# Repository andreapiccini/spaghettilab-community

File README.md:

<p align="center">
  <a href="https://spaghetti-lab.my.canva.site/">Website</a> •
  <a href="https://spaghetti-lab.my.canva.site/join-newsletter">Newsletter</a>
</p>

# SpaghettiLAB Community

From prototype to product.

SpaghettiLAB Community is the open development platform for learning,
experimenting, and building modular embedded and IoT prototypes. It includes
reference hardware, firmware, local software, protocols, integrations, tests,
and examples without artificial feature restrictions.

A prototype is not automatically suitable for production. Professional
deployments also require qualified hardware, secure provisioning, verified
updates, release traceability, lifecycle maintenance, and accountable support.
Those production capabilities are developed and delivered separately so that
organizations can adopt SpaghettiLAB without weakening the open Community
platform.

## Repository structure

- `hardware/` — Core, Backbone, and Module reference designs.
- `firmware/` — Community firmware, SDKs, examples, and verification.
- `software/` — Local Studio, dashboard, Node-RED integration, and packages.
- `contracts/` — Public, language-neutral protocol contracts and golden fixtures.
- `examples/` — End-to-end example systems.
- `docs/` — Documentation licensing and notices.

The Community hardware tree intentionally contains editable KiCad sources, not
generated manufacturing packages. Official production files, factory tooling,
secure provisioning infrastructure, managed cloud services, and commercial
support are maintained separately.

## Open-core model

SpaghettiLAB follows an open-core hardware model with a clear boundary:

- **Community layer:** the source files actually published in this repository,
  licensed under the open-source and open-hardware licences listed below. These
  licences permit commercial use when their conditions are followed.
- **Production layer:** the separately maintained, release-specific package used
  for official commercial products and authorized manufacturing partners.

The Production layer is not part of this repository. It may include validated
Gerber and drill outputs, approved BOM and alternate-part data, pick-and-place
files, panelization and assembly profiles, test fixtures and procedures,
production firmware or provisioning material, enclosure and packaging files,
quality-control criteria, release traceability, and supplier-specific data.
Access to those materials, use of official SpaghettiLAB branding, and the right
to present a product as official or partner-produced require prior written
authorization under a separate commercial or manufacturing agreement.

Anyone may generate their own manufacturing outputs from the public hardware
sources and make or sell products as permitted by CERN-OHL-S-2.0. Such products
must comply with that licence and must not imply official manufacture,
certification, warranty, endorsement, or partnership. See
[`COMMERCIAL.md`](COMMERCIAL.md) and [`TRADEMARK.md`](TRADEMARK.md).

## Hardware projects

- `hardware/core/core.kicad_pro`
- `hardware/backbone/backbone.kicad_pro`
- `hardware/modules/nfc-tag/nfc-tag.kicad_pro`

The KiCad source files embed the symbols and footprints already used by each
design. Some optional 3D models reference the `SPAGHETTI_LIB` environment
variable and are not required to open the schematic or PCB.

## Community and production

The Community platform is intended for education, research, development,
prototyping, and open products. Organizations may evaluate and extend it under
the applicable open-source and open-hardware licenses.

SpaghettiLAB Production adds the controlled engineering work needed to turn a
prototype into a supported product: qualified hardware, secure device identity,
signed releases, manufacturing support, managed updates, fleet operations, and
long-term maintenance.

## Citation

If you use SpaghettiLAB in research, publications, articles, videos, educational
material, or derivative projects, please cite:

> Piccini, A. (2026).  
> SpaghettiLAB: Modular Stackable Electronics Platform.  
> GitHub Repository.  
> https://github.com/andreapiccini/SpaghettiLAB

A machine-readable citation file is available in `CITATION.cff`.

## Licensing

The current Community generation retains the licenses already applied to its
components:

| Content | License |
|---|---|
| Firmware | GPL-3.0-or-later |
| Public applications and services | AGPL-3.0-or-later |
| Protocols and selected integration SDKs | Apache License 2.0 |
| Hardware reference designs | CERN-OHL-S-2.0 |
| Documentation | CC BY 4.0 |

See [`LICENSES.md`](LICENSES.md) for the exact repository map,
[`CONTRIBUTING.md`](CONTRIBUTING.md) for DCO contribution requirements, and
[`TRADEMARK.md`](TRADEMARK.md) for product identity rules. The copyleft transition
does not alter rights granted for earlier versions.

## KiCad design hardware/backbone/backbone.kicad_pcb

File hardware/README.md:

# Hardware sources

The Community repository tracks the editable KiCad projects required to study,
modify and build the public hardware: project, schematic, PCB, symbol, footprint
and related source assets.

Generated manufacturing outputs are intentionally not tracked. This includes
`production/` directories, Gerber and drill files, pick-and-place exports, BOMs,
netlists, fabrication ZIP archives and fabrication-toolkit local options. Generate
them from the reviewed KiCad sources when needed; official manufacturing releases
and production controls are maintained separately.

The ignore rules do not provide confidentiality for files already published in Git
history. They only prevent generated outputs from being added in future commits.

## Backbone V3

Open the [Backbone V3 KiCad project](backbone-v3/backbone-v3.kicad_pro) or the [interactive front panel preview](backbone-v3/anteprima-interattiva.html).

## KiCad library policy

Each public schematic embeds the symbols it uses and each public PCB embeds its
placed footprints, so the existing designs can be opened and edited without the
private Production repository. External 3D models are optional visualization assets:
missing models must not prevent schematic or PCB work.

Do not copy vendor 3D models or global workstation libraries into Community until
their origin and redistribution licence are recorded. New reusable public symbols or
footprints should be added as project-local, redistributable source assets rather
than relying on a developer's global KiCad configuration.

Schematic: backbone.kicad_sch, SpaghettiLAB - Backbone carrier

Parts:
C1, C2: 100nF; C_0402_1005Metric; MPN CL05B104KO5NNNC; LCSC Part Name C1591
C5, C9, C86: 22uF; C_0603_1608Metric; MPN CL10A226MP8NUNE; LCSC Part C86295
C11: 1uF; C_0402_1005Metric; LCSC Part Name C128624
C74: 100nF; C_0402_1005Metric; LCSC Part C1525
C84, C85: 100nF/50V; C_0402_1005Metric; MPN CL05B104KB54PNC; LCSC Part C307331
C129: 100nF; C_0402_1005Metric; MPN CL05B104KO5NNNC; LCSC C1525
C410: 100nF; C_0402_1005Metric; LCSC C1525
D6: SS54_C22452; SMA_L4.4-W2.8-LS5.4-R-RD; MPN SS54; LCSC Part C22452
H1, H2, H3, H4: MountingHole; MountingHole_2.2mm_M2
J2: FROM_PREVIOUS; Magnetic_J2_Aux
J4: SM04B-SRSS-TB(LF)(SN); JST_SH_SM04B-SRSS-TB_1x04-1MP_P1.00mm_Horizontal; MPN SM04B-SRSS-TB(LF)(SN); LCSC C160404
J9: TO NEXT; Magnetic_J9_Aux
J17, J18, J19, J20, J22, J23, J31, J32, J33, J34: HX PM2.54-1x8P TP-YQ; Hanxia_C42380985_1x08_BottomAccess_Trial; MPN HX PM2.54-1x8P TP-YQ; LCSC C42380985
J30, J35: SM06B-GHS-TB; JST_GH_SM06B-GHS-TB_1x06-1MP_P1.25mm_Horizontal; MPN SM06B-GHS-TB(LF)(SN); LCSC C133065
L1: 3.3uH; L_XRTC404012S; MPN XRTC404012S3R3MBCA; LCSC Part C39846848
Q2: AO3401A; SOT-23_L2.9-W1.3-P1.90-LS2.4-BR; MPN AO3401A; LCSC Part C15127
Q3, Q4, Q5, Q6, Q7, Q8, Q21, Q22, Q23, Q24, Q25, Q26, Q27, Q28, Q29, Q30: AO6604; SOT-23-6_L2.9-W1.6-P0.95-LS2.8-BL; MPN AO6604; LCSC C5182068
R4: 10k; R_0402_1005Metric; MPN 0402WGF1002TCE; LCSC Part Name C25804
R5: 470R; R_0402_1005Metric; MPN 0402WGF4700TCE; LCSC Part Name C23179
R8: 120R; R_0402_1005Metric; MPN 0402WGF1200TCE; LCSC Part Name C2906988
R15, R16: 10k; R_0402_1005Metric; LCSC Part C25744
R17, R18: 33R; R_0402_1005Metric; LCSC Part C25105
R22, R27: 5.1k; R_0402_1005Metric; LCSC Part C25905
R24, R25, R440, R441: 4.7k; R_0402_1005Metric; LCSC C25900
R36: 33k 1%; R_0402_1005Metric; MPN 0402WGF3302TCE; LCSC Part C25779
R37: 10k 1%; R_0402_1005Metric; MPN 0402WGF1002TCE; LCSC Part C25744
R104: 47k; R_0402_1005Metric; MPN 0402WGF4702TCE; LCSC C25792
R443: 10k; R_0402_1005Metric; LCSC C25744
RN1, RN4, RN7, RN10: 4x100k; R_Array_Convex_4x0402; MPN 4D02WGJ0104TCE; LCSC C25724
RN2, RN5, RN8, RN11: 4x4.7k; R_Array_Convex_4x0402; MPN 4D02WGJ0472TCE; LCSC C29586
U1: ESP32-S3-MINI-1-N4R2; ESP32-S3-MINI-1_Backbone; MPN ESP32-S3-MINI-1-N4R2; LCSC C3013941
U2: SIT1051AQTK/3; DFN-8-1EP_3x3mm_P0.65mm_EP1.5x2.3mm; MPN SIT1051AQTK/3; LCSC Part C5382549
U3: HC-TYPE-C-16P-01A; USB-C-SMD_HC-TYPE-C-16P-01A; MPN HC-TYPE-C-16P-01A; LCSC Part C2894897
U4: TPS562201DDCR; TSOT-23-6_Power; MPN TPS562201DDCR; LCSC Part C90061
U8: GAQY221S; SMD-4_L4.6-W3.7-P2.54-LS7.0-TL; MPN GAQY221S; LCSC Part C7435105
U25, U73: TCA9555RTWR(UMW); WQFN-24-1EP_4x4mm_P0.5mm_EP2.45x2.45mm; MPN TCA9555RTWR; LCSC C42420609

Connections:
5V: C1.1, C5.1, C85.1, C129.1, C410.1, D6.2 (K), J2.1, J9.1, J30.1 (5V), J35.1 (5V), Q2.2 (S), R4.1, U2.3 (VCC), U4.3 (VIN), U4.5 (EN), U25.21 (VCC), U73.21 (VCC), U73.23 (A1); also elsewhere on the board
/BOOT: R15.2, U1.4 (IO0)
/BUCK_BOOT: C84.1, U4.6 (VBST)
/BUCK_FB: R36.2, R37.1, U4.4 (VFB)
/BUCK_SW: C84.2, L1.1, U4.2 (SW)
/TERM_DRIVE: Q2.3 (D), R5.2
/TERM_LED: R5.1, U8.1
/TERM_R: R8.2, U8.3
/USB_CC1: R22.1, U3.A5 (CC1)
/USB_CC2: R27.2, U3.B5 (CC2)
A0: U1.11 (IO7); also elsewhere on the board
A1: U1.12 (IO8); also elsewhere on the board
A2: U1.14 (IO10); also elsewhere on the board
A3: U1.13 (IO9); also elsewhere on the board
A4: U1.5 (IO1); also elsewhere on the board
A5: U1.6 (IO2); also elsewhere on the board
CAN_N: J2.2, J9.2, J30.3 (CAN_L), J35.3 (CAN_L), U2.6 (CANL), U8.4; also elsewhere on the board
CAN_P: J2.3, J9.3, J30.2 (CAN_H), J35.2 (CAN_H), R8.1, U2.7 (CANH); also elsewhere on the board
CAN_RX: U1.34 (IO38), U2.4 (RXD)
CAN_TX: R104.2, U1.35 (IO39), U2.1 (TXD)
ESP_A6: U1.7 (IO3); also elsewhere on the board
ESP_A7: U1.8 (IO4); also elsewhere on the board
ESP_UP1: U1.9 (IO5); also elsewhere on the board
ESP_UP2: U1.10 (IO6); also elsewhere on the board
ESP_UP3: U1.21 (IO17); also elsewhere on the board
ESP_UP4: U1.22 (IO18); also elsewhere on the board
ESP_UP5: U1.19 (IO15); also elsewhere on the board
ESP_UP6: U1.20 (IO16); also elsewhere on the board
ESP_UP7: U1.18 (IO14); also elsewhere on the board
ESP_UP8: U1.17 (IO13); also elsewhere on the board
EXP_SPI_CS_N: R443.2, U1.28 (IO33)
GND: C1.2, C2.2, C5.2, C9.2, C11.1, C74.1, C85.2, C86.2, C129.2, C410.2, J2.4, J4.1 (GND), J9.4, J30.4 (GND), J30.6 (GND), J30.MP, J35.4 (GND), J35.6 (GND), J35.MP, Q3.5 (S), Q4.5 (S), Q5.5 (S), Q6.5 (S), Q7.5 (S), Q8.5 (S), Q21.5 (S), Q22.5 (S), Q23.5 (S), Q24.5 (S), Q25.5 (S), Q26.5 (S), Q27.5 (S), Q28.5 (S), Q29.5 (S), Q30.5 (S), R22.2, R27.1, R37.2, RN2.5, RN2.6, RN2.7, RN2.8, RN5.5, RN5.6, RN5.7, RN5.8, RN8.1, RN8.2, RN8.3, RN8.4, RN11.5, RN11.6, RN11.7, RN11.8, U1.1 (GND), U1.2 (GND), U1.42 (GND), U1.43 (GND), U1.46 (GND), U1.47 (GND), U1.48 (GND), U1.49 (GND), U1.50 (GND), U1.51 (GND), U1.52 (GND), U1.53 (GND), U1.54 (GND), U1.55 (GND), U1.56 (GND), U1.57 (GND), U1.58 (GND), U1.59 (GND), U1.60 (GND), U1.61 (GND), U1.62 (GND), U1.63 (GND), U1.64 (GND), U1.65 (GND), U2.2 (GND), U2.8 (S), U2.9 (EP), U3.1 (SHELL), U3.2 (SHELL), U3.3 (SHELL), U3.4 (SHELL), U3.A1B12 (GND), U3.B1A12 (GND), U4.1 (GND), U8.2, U25.9 (GND), U25.18 (A0), U25.23 (A1), U25.24 (A2), U25.25 (EP), U73.9 (GND), U73.18 (A0), U73.24 (A2), U73.25 (EP); also elsewhere on the board
I2C5_SCL: U25.19 (SCL), U73.19 (SCL); also elsewhere on the board
I2C5_SDA: U25.20 (SDA), U73.20 (SDA); also elsewhere on the board
I2C_CTRL_SCL: R441.2, U1.27 (IO47); also elsewhere on the board
I2C_CTRL_SDA: R440.2, U1.25 (IO21); also elsewhere on the board
IO11: U1.15 (IO11)
IO34: U1.29 (IO34); also elsewhere on the board
IO36: U1.32 (IO36); also elsewhere on the board
IO40: U1.36 (IO40)
IO41: U1.37 (IO41)
IO45: U1.41 (IO45)
IO46: U1.44 (IO46)
N_GATE_0: Q3.1 (G), RN2.4, U25.2 (P01)
N_GATE_1: Q4.1 (G), RN2.3, U25.4 (P03)
N_GATE_2: Q5.1 (G), RN2.2, U25.6 (P05)
N_GATE_3: Q6.1 (G), RN2.1, U25.8 (P07)
N_GATE_4: Q7.1 (G), RN5.4, U25.11
N_GATE_5: Q8.1 (G), RN5.3, U25.13
PORT_A0: J18.1, J19.1, J23.1, J33.1, J34.1, Q3.4 (D), Q3.6 (D); also elsewhere on the board
PORT_A1: J18.2, J19.2, J23.2, J33.2, J34.2, Q4.4 (D), Q4.6 (D); also elsewhere on the board
PORT_A2: J18.3, J19.3, J23.3, J33.3, J34.3, Q5.4 (D), Q5.6 (D); also elsewhere on the board
PORT_A3: J18.4, J19.4, J23.4, J33.4, J34.4, Q6.4 (D), Q6.6 (D); also elsewhere on the board
PORT_A4: J18.5, J19.5, J23.5, J33.5, J34.5, Q7.4 (D), Q7.6 (D); also elsewhere on the board
PORT_A5: J18.6, J19.6, J23.6, J33.6, J34.6, Q8.4 (D), Q8.6 (D); also elsewhere on the board
PORT_A6: J18.7, J19.7, J23.7, J33.7, J34.7, Q29.4 (D), Q29.6 (D); also elsewhere on the board
PORT_A6_NG: Q29.1 (G), RN5.2, U25.15
PORT_A6_PG: Q29.3 (G), RN4.7, U25.14
PORT_A7: J18.8, J19.8, J23.8, J33.8, J34.8, Q30.4 (D), Q30.6 (D); also elsewhere on the board
PORT_A7_NG: Q30.1 (G), RN5.1, U25.17
PORT_A7_PG: Q30.3 (G), RN4.8, U25.16
P_GATE_0: Q3.3 (G), RN1.8, U25.1 (P00)
P_GATE_1: Q4.3 (G), RN1.7, U25.3 (P02)
P_GATE_2: Q5.3 (G), RN1.6, U25.5 (P04)
P_GATE_3: Q6.3 (G), RN1.5, U25.7 (P06)
P_GATE_4: Q7.3 (G), RN4.5, U25.10
P_GATE_5: Q8.3 (G), RN4.6, U25.12
RGB_DIN_3V3: U1.30 (IO48); also elsewhere on the board
SPI_MISO: U1.40 (RXD0)
SPI_MOSI: U1.39 (TXD0)
SPI_SCLK: U1.38 (IO42)
TERM_CTRL_IN: J2.5, J30.5 (TERM); also elsewhere on the board
TERM_CTRL_OUT: J9.5, J35.5 (TERM); also elsewhere on the board
TERM_GATE_N: Q2.1 (G), R4.2; also elsewhere on the board
TWI_SCL: J4.4 (SCL), R25.2, U1.31 (IO35)
TWI_SDA: J4.3 (SDA), R24.2, U1.33 (IO37)
UP1: J17.1, J20.1, J22.1, J31.1, J32.1, Q21.4 (D), Q21.6 (D); also elsewhere on the board
UP1_NG: Q21.1 (G), RN8.8, U73.2 (P01)
UP1_PG: Q21.3 (G), RN7.8, U73.1 (P00)
UP2: J17.2, J20.2, J22.2, J31.2, J32.2, Q22.4 (D), Q22.6 (D); also elsewhere on the board
UP2_NG: Q22.1 (G), RN8.7, U73.4 (P03)
UP2_PG: Q22.3 (G), RN7.7, U73.3 (P02)
UP3: J17.3, J20.3, J22.3, J31.3, J32.3, Q23.4 (D), Q23.6 (D); also elsewhere on the board
UP3_NG: Q23.1 (G), RN8.6, U73.6 (P05)
UP3_PG: Q23.3 (G), RN7.6, U73.5 (P04)
UP4: J17.4, J20.4, J22.4, J31.4, J32.4, Q24.4 (D), Q24.6 (D); also elsewhere on the board
UP4_NG: Q24.1 (G), RN8.5, U73.8 (P07)
UP4_PG: Q24.3 (G), RN7.5, U73.7 (P06)
UP5: J17.5, J20.5, J22.5, J31.5, J32.5, Q25.4 (D), Q25.6 (D); also elsewhere on the board
UP5_NG: Q25.1 (G), RN11.4, U73.11
UP5_PG: Q25.3 (G), RN10.8, U73.10
UP6: J17.6, J20.6, J22.6, J31.6, J32.6, Q26.4 (D), Q26.6 (D); also elsewhere on the board
UP6_NG: Q26.1 (G), RN11.3, U73.13
UP6_PG: Q26.3 (G), RN10.7, U73.12
UP7: J17.7, J20.7, J22.7, J31.7, J32.7, Q27.4 (D), Q27.6 (D); also elsewhere on the board
UP7_NG: Q27.1 (G), RN11.2, U73.15
UP7_PG: Q27.3 (G), RN10.6, U73.14
UP8: J17.8, J20.8, J22.8, J31.8, J32.8, Q28.4 (D), Q28.6 (D); also elsewhere on the board
UP8_NG: Q28.1 (G), RN11.1, U73.17
UP8_PG: Q28.3 (G), RN10.5, U73.16
USB_D+: R17.1, U3.A6 (D+), U3.B6 (D+)
USB_D-: R18.1, U3.A7 (D-), U3.B7 (D-)
USB_ESP_D+: R17.2, U1.24 (USB_D+)
USB_ESP_D-: R18.2, U1.23 (USB_D-)
VBUS: D6.1 (A), U3.A4B9 (VBUS), U3.B4A9 (VBUS)
VCORE: C2.1, C9.1, C74.2, C86.1, J4.2 (+3V3), L1.2, R15.1, R16.1, R24.1, R25.1, R36.1, R104.1, R440.1, R441.1, R443.1, U1.3 (3V3), U2.5 (VIO); also elsewhere on the board
VPORT: Q3.2 (S), Q4.2 (S), Q5.2 (S), Q6.2 (S), Q7.2 (S), Q8.2 (S), Q21.2 (S), Q22.2 (S), Q23.2 (S), Q24.2 (S), Q25.2 (S), Q26.2 (S), Q27.2 (S), Q28.2 (S), Q29.2 (S), Q30.2 (S), RN1.1, RN1.2, RN1.3, RN1.4, RN4.1, RN4.2, RN4.3, RN4.4, RN7.1, RN7.2, RN7.3, RN7.4, RN10.1, RN10.2, RN10.3, RN10.4; also elsewhere on the board
VPORT_SEL: U1.16 (IO12); also elsewhere on the board
~RESET: C11.2, R16.2, U1.45 (EN)

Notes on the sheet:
U1 | OPTIONAL ESP32-S3
Connects row P1 to its ESP signal, 3.3 V, ground or high impedance.
P4 | CONFIGURABLE EXPERIMENT ROW
RN1-RN11 | RESISTOR ARRAYS
U25 | SHARED PORT CONFIGURATION
Hanxia 1x8 | 2.54 mm pin pitch, 6.85 mm per pair, 7.62 mm between middle rows
USB-C | COMPUTER CONNECTION
Connects row P3 to its ESP signal, 3.3 V, ground or high impedance.
LOWER PORTS 7 / 8 | CONFIGURABLE EXPERIMENT ROWS
Powers the standalone Backbone.
Connects row P4 to its ESP signal, 3.3 V, ground or high impedance.
Connects compatible sensors through a four-wire cable.
J4 | QWIIC SENSOR LINK
P1 | CONFIGURABLE EXPERIMENT ROW
P1-P6 = external experiment rows | A0-A5 = ESP-side signals | J17 / J20: upper rows 1–8. J18 / J19: lower rows 1–8.
U2 | CAN TRANSCEIVER
Adds Wi-Fi, Bluetooth and familiar ESP32 development tools.
J26 | GH EXPANSION PORT
SPI and CAN on JST GH 10-pin. 5V_EXP current-limited by U5 (~1.9 A, EN = IO37).
P2 | CONFIGURABLE EXPERIMENT ROW
UPPER PORTS 1–8 | CONFIGURABLE EXPERIMENT ROWS
READING GUIDE: Pn = row / connector | Q = power switch | U12/U13 = signal isolation | RN = isolated resistor arrays
Passes power and messages between neighbouring backbones.
Same circuit repeats for P1-P6. Never enable P-MOS and N-MOS together. Set GPIO Hi-Z before changing power mode.
UPPER PORT RAIL CONTROL | U73 AT I2C 0x22
Functional groups | local wires retained | power shown with symbols | cross-block links use named nets
Connects row P6 to its ESP signal, 3.3 V, ground or high impedance.
One symbol per physical 4x array (0402x4). Pins connect by net name to the port rows.
GPIO35/36/37 AUX links: free on ESP32-S3-MINI-1-N4R2 (quad PSRAM). IO26 is reserved by the PSRAM. USB does not pass through FPGA logic.
Connects row P2 to its ESP signal, 3.3 V, ground or high impedance.
J2 and J9 detect both neighbours. Q2/U8 connect 120 ohms when either link is open. See CAN termination.
Connects row P5 to its ESP signal, 3.3 V, ground or high impedance.
J2 / J9 | MAGNETIC CAN LINK
P3 | CONFIGURABLE EXPERIMENT ROW
P6 | CONFIGURABLE EXPERIMENT ROW
The ESP32 controls the experiment ports over the internal I2C bus.
P5 | CONFIGURABLE EXPERIMENT ROW
Connects USB to the ESP32.
J17 / J20: eight configurable upper rows. J18 / J19: eight configurable lower rows.
SPAGHETTILAB | BACKBONE CARRIER

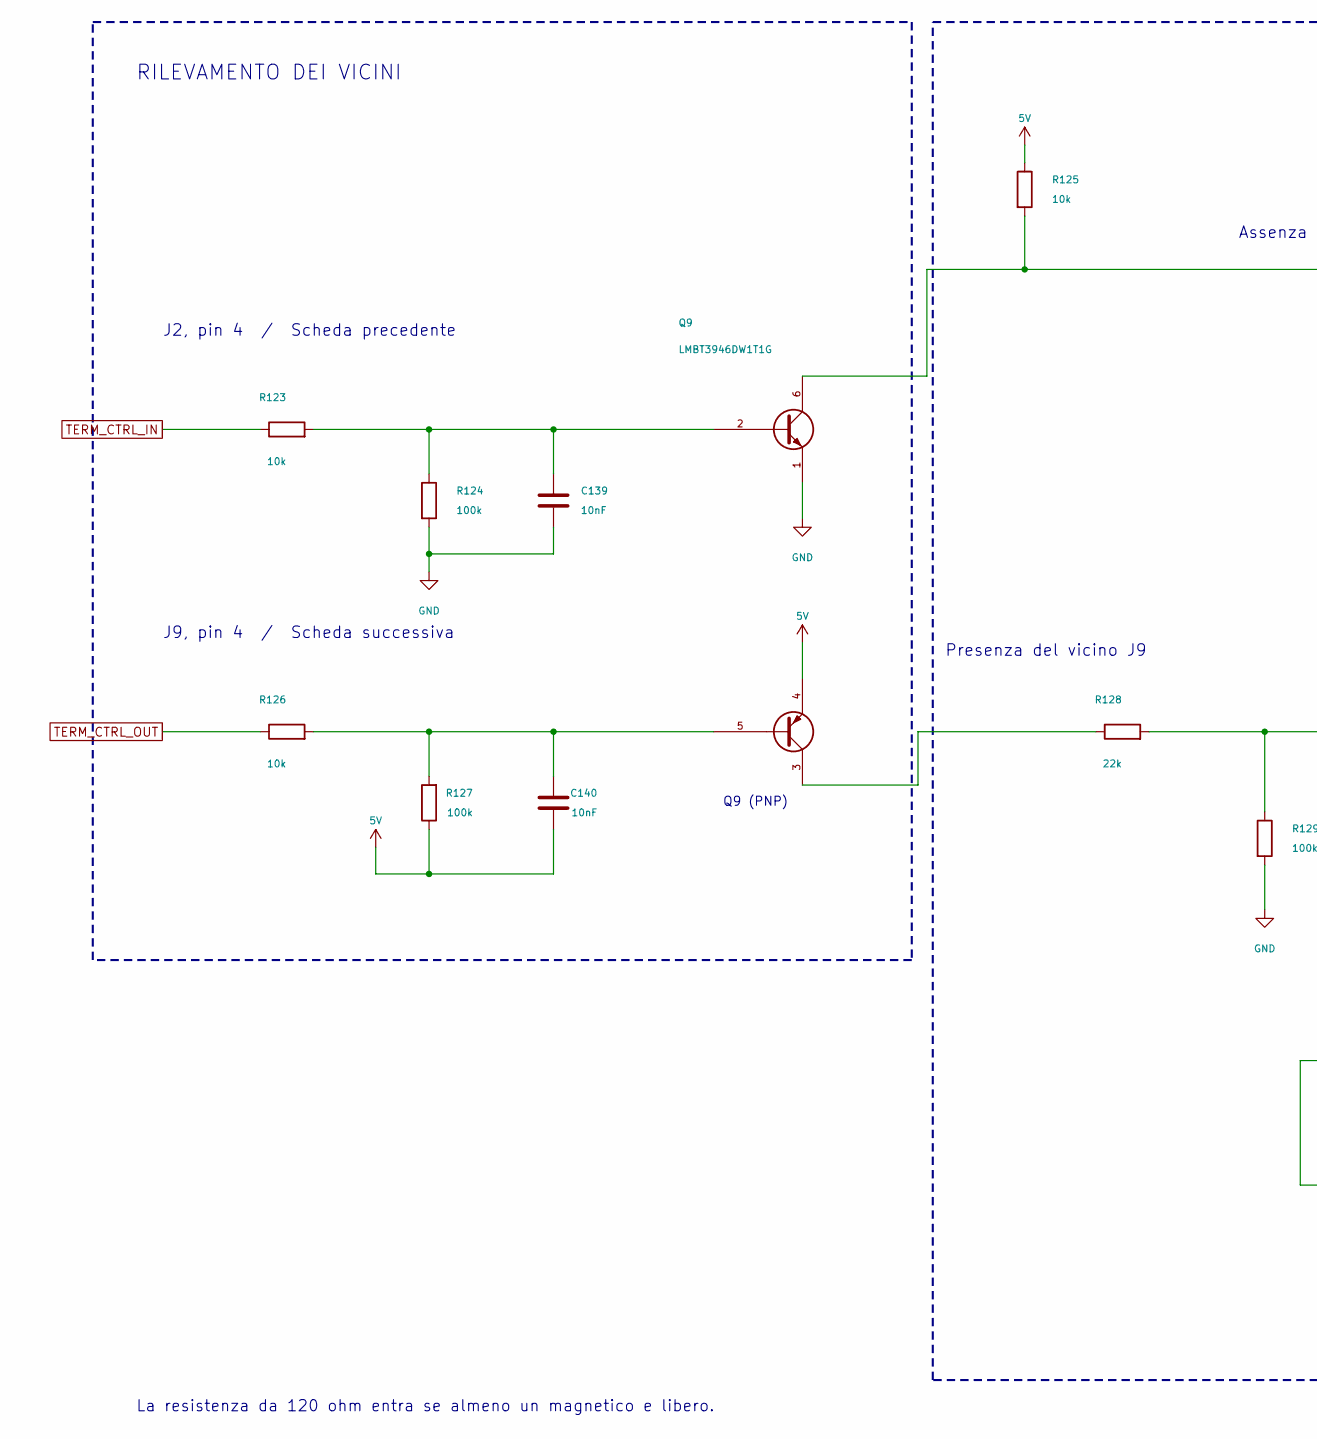
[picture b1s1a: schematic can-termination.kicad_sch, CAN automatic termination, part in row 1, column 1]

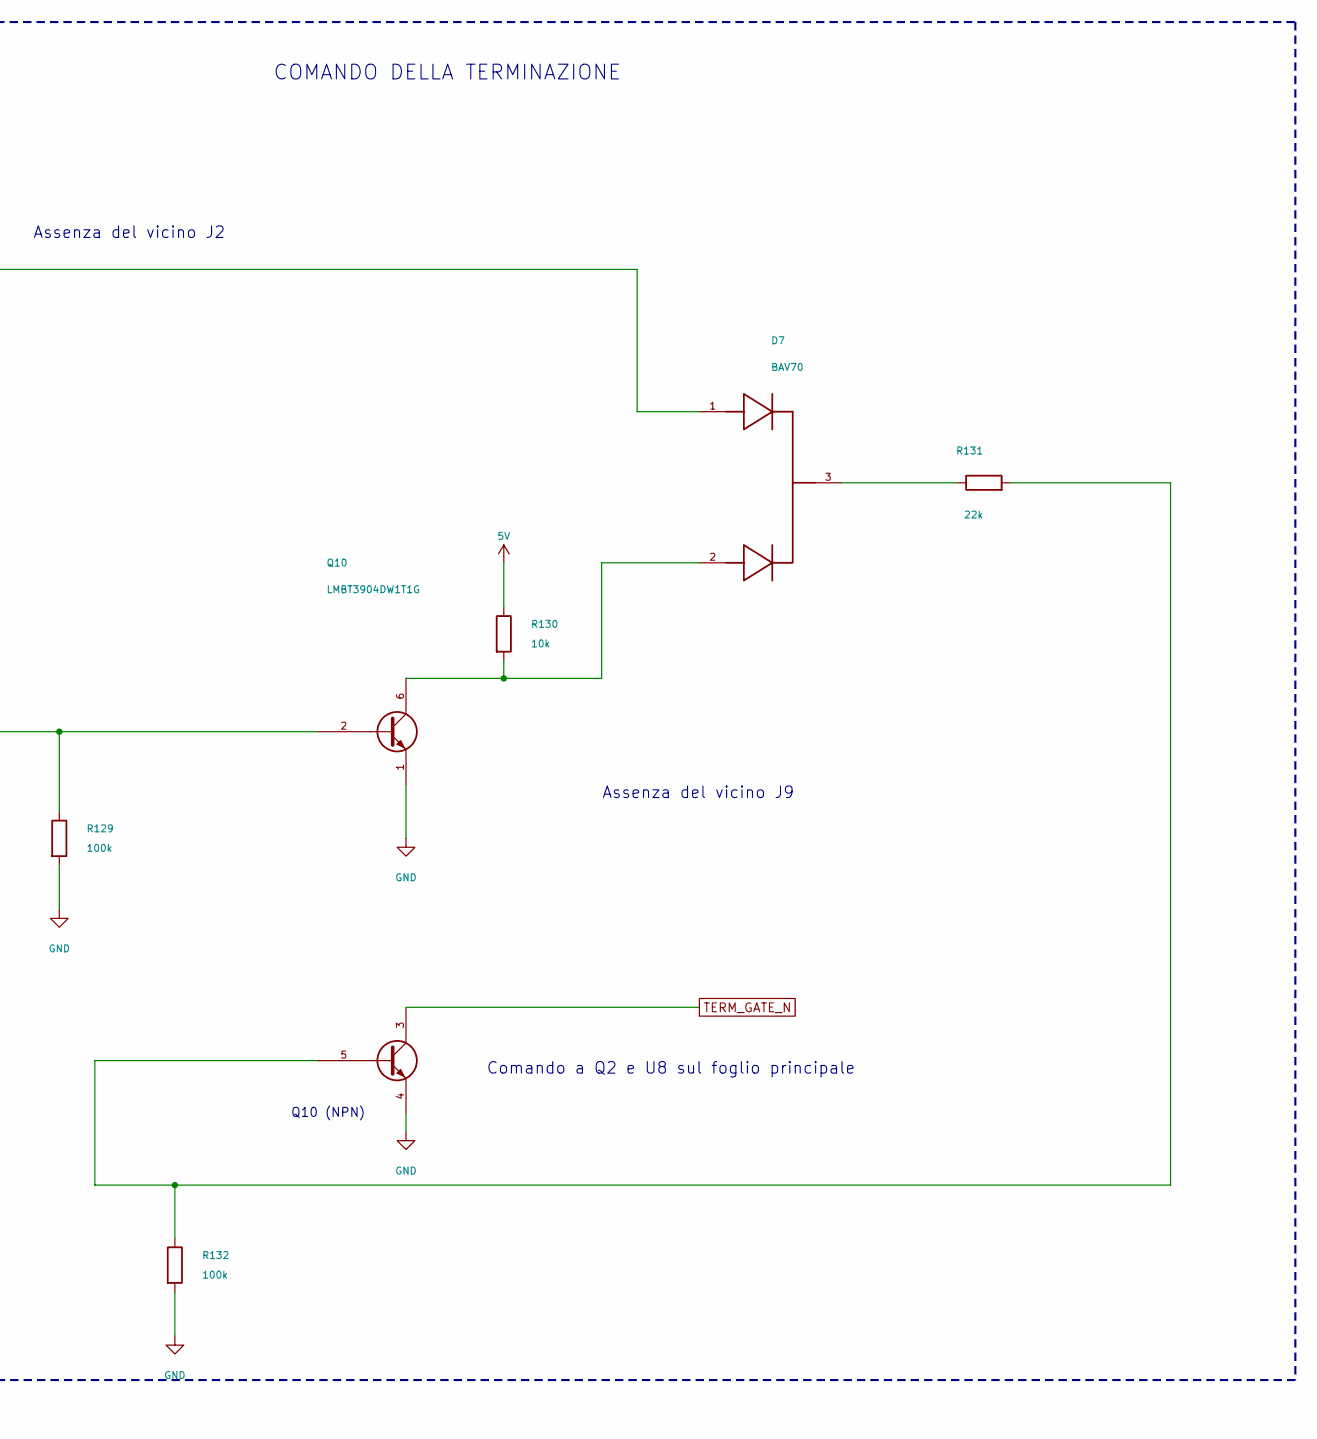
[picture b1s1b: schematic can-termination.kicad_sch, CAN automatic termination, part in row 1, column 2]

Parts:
C139, C140: 10nF; C_0402_1005Metric; MPN CL05B103KB5NNNC; LCSC C15195
D7: BAV70; SOT-23; MPN BAV70; LCSC C68978
Q9: LMBT3946DW1T1G; SOT-363_SC-70-6; MPN LMBT3946DW1T1G; LCSC C136169
Q10: LMBT3904DW1T1G; SOT-363_SC-70-6; MPN LMBT3904DW1T1G; LCSC C131781
R123, R125, R126, R130: 10k; R_0402_1005Metric; MPN 0402WGF1002TCE; LCSC C25744
R124, R127, R129, R132: 100k; R_0402_1005Metric; MPN 0402WGF1003TCE; LCSC C25741
R128, R131: 22k; R_0402_1005Metric; MPN 0402WGF2202TCE; LCSC C25768

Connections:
5V: C140.1, Q9.4 (E), R125.1, R127.1, R130.1; also elsewhere on the board
GND: C139.2, Q9.1 (E), Q10.1 (E), Q10.4 (E), R124.2, R129.2, R132.2; also elsewhere on the board
unnamed: C139.1, Q9.2 (B), R123.2, R124.1
unnamed: C140.2, Q9.5 (B), R126.2, R127.2
unnamed: D7.1 (A), Q9.6 (C), R125.2
unnamed: D7.2 (A), Q10.6 (C), R130.2
unnamed: D7.3 (K), R131.1
unnamed: Q9.3 (C), R128.1
unnamed: Q10.2 (B), R128.2, R129.1
unnamed: Q10.5 (B), R131.2, R132.1
TERM_CTRL_IN: R123.1; also elsewhere on the board
TERM_CTRL_OUT: R126.1; also elsewhere on the board
TERM_GATE_N: Q10.3 (C); also elsewhere on the board

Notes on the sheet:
Q9 (PNP)
Assenza del vicino J9
La resistenza da 120 ohm entra se almeno un magnetico e libero.
COMANDO DELLA TERMINAZIONE
Comando a Q2 e U8 sul foglio principale
J2, pin 4 / Scheda precedente
J9, pin 4 / Scheda successiva
Q10 (NPN)
RILEVAMENTO DEI VICINI
Assenza del vicino J2
Presenza del vicino J9

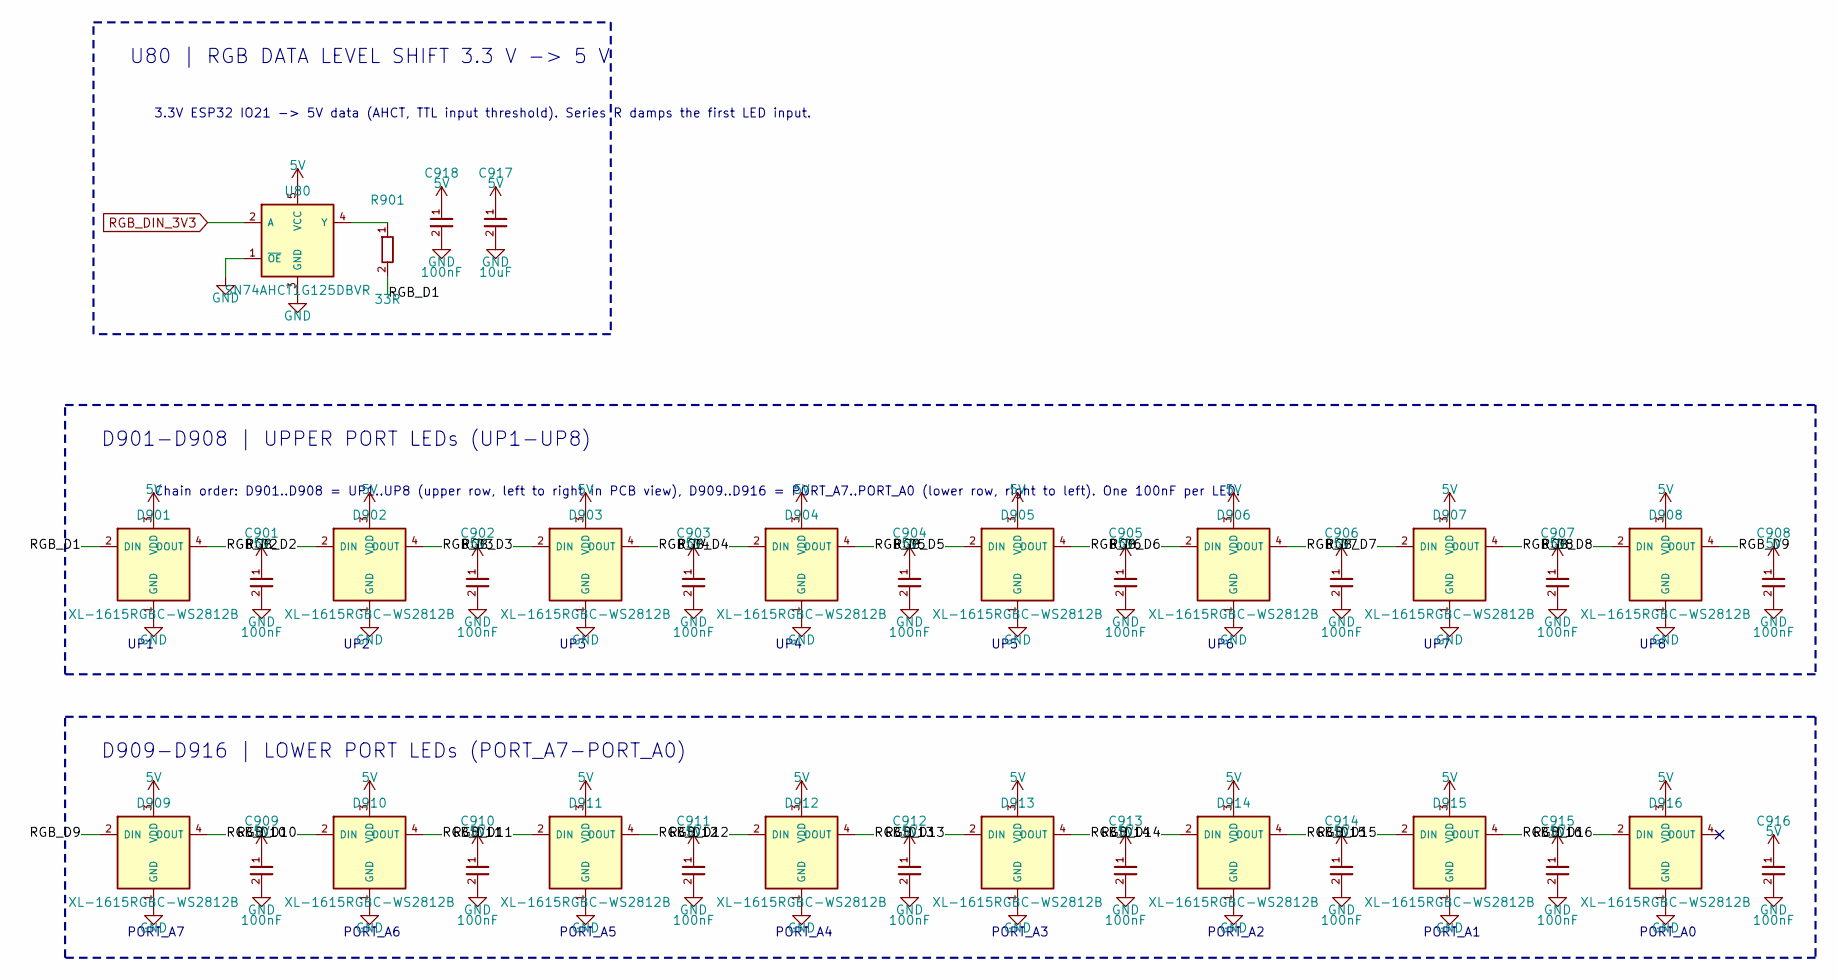
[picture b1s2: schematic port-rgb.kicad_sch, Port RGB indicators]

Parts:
C901, C902, C903, C904, C905, C906, C907, C908, C909, C910, C911, C912, C913, C914, C915, C916, C918: 100nF; C_0402_1005Metric; LCSC C1525
C917: 10uF; C_0603_1608Metric; LCSC C19702
D901, D902, D903, D904, D905, D906, D907, D908, D909, D910, D911, D912, D913, D914, D915, D916: XL-1615RGBC-WS2812B; LED-SMD_4P-L1.6-W1.5_XL-1615RGBC-WS2812B-1; LCSC C5349954
R901: 33R; R_0402_1005Metric; LCSC C25105
U80: SN74AHCT1G125DBVR; SOT-23-5; LCSC C7484

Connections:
5V: C901.1, C902.1, C903.1, C904.1, C905.1, C906.1, C907.1, C908.1, C909.1, C910.1, C911.1, C912.1, C913.1, C914.1, C915.1, C916.1, C917.1, C918.1, D901.3 (VDD), D902.3 (VDD), D903.3 (VDD), D904.3 (VDD), D905.3 (VDD), D906.3 (VDD), D907.3 (VDD), D908.3 (VDD), D909.3 (VDD), D910.3 (VDD), D911.3 (VDD), D912.3 (VDD), D913.3 (VDD), D914.3 (VDD), D915.3 (VDD), D916.3 (VDD), U80.5 (VCC); also elsewhere on the board
/Port RGB/RGB_D1: D901.2 (DIN), R901.2
/Port RGB/RGB_D2: D901.4 (DOUT), D902.2 (DIN)
/Port RGB/RGB_D3: D902.4 (DOUT), D903.2 (DIN)
/Port RGB/RGB_D4: D903.4 (DOUT), D904.2 (DIN)
/Port RGB/RGB_D5: D904.4 (DOUT), D905.2 (DIN)
/Port RGB/RGB_D6: D905.4 (DOUT), D906.2 (DIN)
/Port RGB/RGB_D7: D906.4 (DOUT), D907.2 (DIN)
/Port RGB/RGB_D8: D907.4 (DOUT), D908.2 (DIN)
/Port RGB/RGB_D9: D908.4 (DOUT), D909.2 (DIN)
/Port RGB/RGB_D10: D909.4 (DOUT), D910.2 (DIN)
/Port RGB/RGB_D11: D910.4 (DOUT), D911.2 (DIN)
/Port RGB/RGB_D12: D911.4 (DOUT), D912.2 (DIN)
/Port RGB/RGB_D13: D912.4 (DOUT), D913.2 (DIN)
/Port RGB/RGB_D14: D913.4 (DOUT), D914.2 (DIN)
/Port RGB/RGB_D15: D914.4 (DOUT), D915.2 (DIN)
/Port RGB/RGB_D16: D915.4 (DOUT), D916.2 (DIN)
GND: C901.2, C902.2, C903.2, C904.2, C905.2, C906.2, C907.2, C908.2, C909.2, C910.2, C911.2, C912.2, C913.2, C914.2, C915.2, C916.2, C917.2, C918.2, D901.1 (GND), D902.1 (GND), D903.1 (GND), D904.1 (GND), D905.1 (GND), D906.1 (GND), D907.1 (GND), D908.1 (GND), D909.1 (GND), D910.1 (GND), D911.1 (GND), D912.1 (GND), D913.1 (GND), D914.1 (GND), D915.1 (GND), D916.1 (GND), U80.1 (~OE), U80.3 (GND); also elsewhere on the board
unnamed: R901.1, U80.4 (Y)
RGB_DIN_3V3: U80.2 (A); also elsewhere on the board

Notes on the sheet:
UP5
PORT_A6
UP8
PORT_A1
3.3V ESP32 IO21 -> 5V data (AHCT, TTL input threshold). Series R damps the first LED input.
U80 | RGB DATA LEVEL SHIFT 3.3 V -> 5 V
UP2
PORT_A4
Chain order: D901..D908 = UP1..UP8 (upper row, left to right in PCB view), D909..D916 = PORT_A7..PORT_A0 (lower row, right to left). One 100nF per LED.
UP3
UP7
PORT_A0
PORT_A7
D909-D916 | LOWER PORT LEDs (PORT_A7-PORT_A0)
UP6
PORT_A3
D901-D908 | UPPER PORT LEDs (UP1-UP8)
UP4
PORT_A2
PORT_A5
UP1

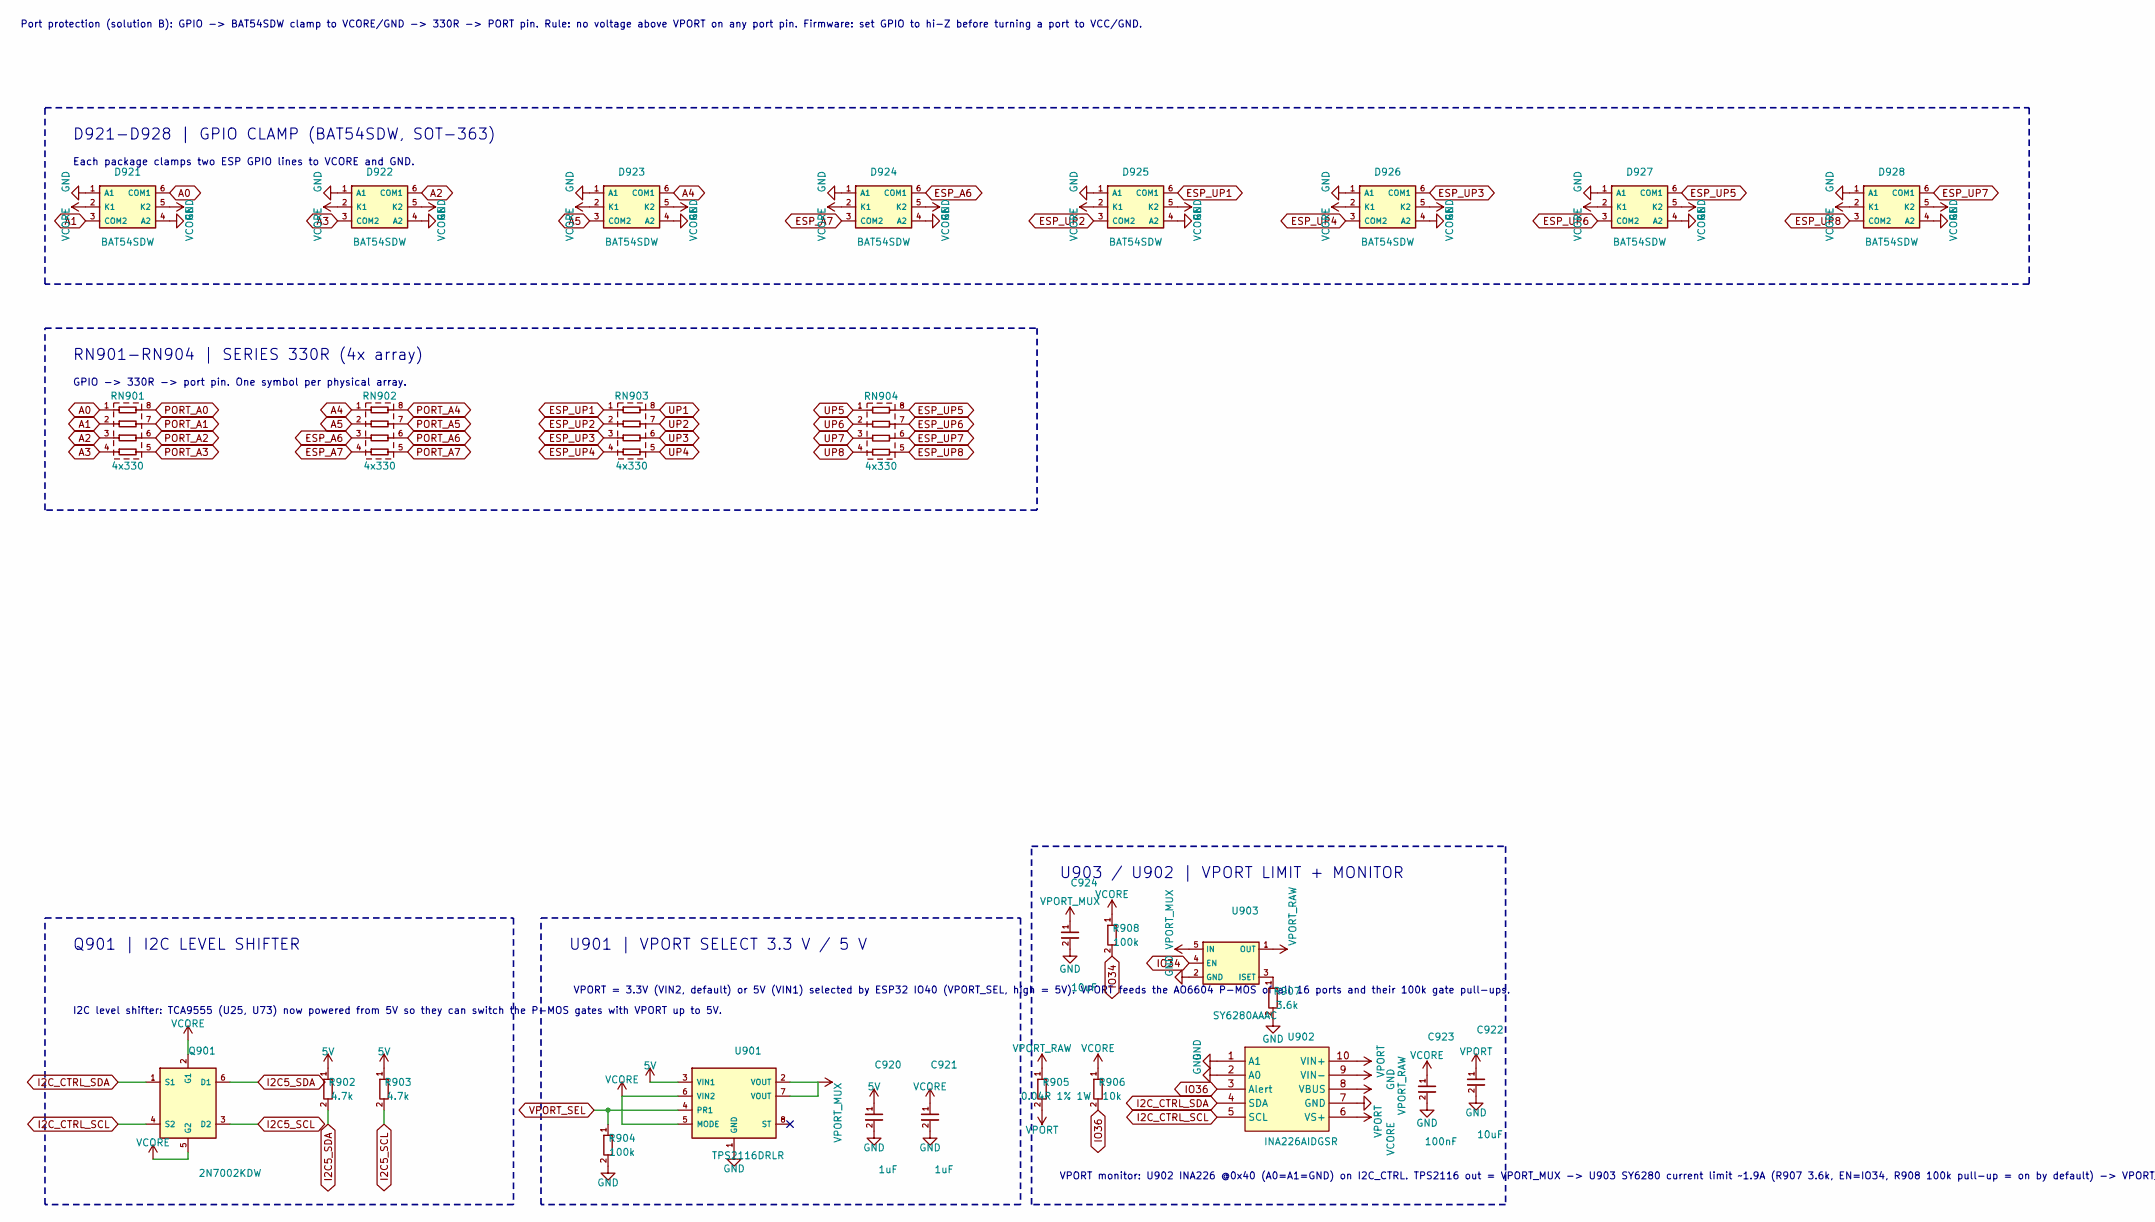
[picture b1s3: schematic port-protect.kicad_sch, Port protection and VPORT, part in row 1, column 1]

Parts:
C920, C921: 1uF; C_0402_1005Metric; LCSC C52923
C922: 10uF; C_0603_1608Metric; LCSC C19702
C923: 100nF; C_0402_1005Metric; LCSC C1525
C924: 10uF; C0603; LCSC C19702
D921, D922, D923, D924, D925, D926, D927, D928: BAT54SDW; SOT-363_SC-70-6; LCSC C2919793
Q901: 2N7002KDW; SOT-363_SC-70-6; LCSC C106992
R902, R903: 4.7k; R_0402_1005Metric; LCSC C25900
R904, R908: 100k; R_0402_1005Metric; LCSC C25741
R905: 0.04R 1% 1W; R_1206_3216Metric; LCSC C5375400
R906: 10k; R_0402_1005Metric; LCSC C25744
R907: 3.6k; R_0402_1005Metric; LCSC C25891
RN901, RN902, RN903, RN904: 4x330; R_Array_Convex_4x0402; LCSC C43557
U901: TPS2116DRLR; SOT-583-8_L2.1-W1.6-P0.50-LS1.6-BL; LCSC C3235557
U902: INA226AIDGSR; MSOP-10_L3.0-W3.0-P0.50-LS5.0-BL; LCSC C49851
U903: SY6280AAAC; SOT-23-5; LCSC C207620

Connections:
5V: C920.1, R902.1, R903.1, U901.3 (VIN1); also elsewhere on the board
A0: D921.6 (COM1), RN901.1; also elsewhere on the board
A1: D921.3 (COM2), RN901.2; also elsewhere on the board
A2: D922.6 (COM1), RN901.3; also elsewhere on the board
A3: D922.3 (COM2), RN901.4; also elsewhere on the board
A4: D923.6 (COM1), RN902.1; also elsewhere on the board
A5: D923.3 (COM2), RN902.2; also elsewhere on the board
ESP_A6: D924.6 (COM1), RN902.3; also elsewhere on the board
ESP_A7: D924.3 (COM2), RN902.4; also elsewhere on the board
ESP_UP1: D925.6 (COM1), RN903.1; also elsewhere on the board
ESP_UP2: D925.3 (COM2), RN903.2; also elsewhere on the board
ESP_UP3: D926.6 (COM1), RN903.3; also elsewhere on the board
ESP_UP4: D926.3 (COM2), RN903.4; also elsewhere on the board
ESP_UP5: D927.6 (COM1), RN904.8; also elsewhere on the board
ESP_UP6: D927.3 (COM2), RN904.7; also elsewhere on the board
ESP_UP7: D928.6 (COM1), RN904.6; also elsewhere on the board
ESP_UP8: D928.3 (COM2), RN904.5; also elsewhere on the board
GND: C920.2, C921.2, C922.2, C923.2, C924.2, D921.1 (A1), D921.4 (A2), D922.1 (A1), D922.4 (A2), D923.1 (A1), D923.4 (A2), D924.1 (A1), D924.4 (A2), D925.1 (A1), D925.4 (A2), D926.1 (A1), D926.4 (A2), D927.1 (A1), D927.4 (A2), D928.1 (A1), D928.4 (A2), R904.2, R907.2, U901.1 (GND), U902.1 (A1), U902.2 (A0), U902.7 (GND), U903.2 (GND); also elsewhere on the board
I2C5_SCL: Q901.3 (D2), R903.2; also elsewhere on the board
I2C5_SDA: Q901.6 (D1), R902.2; also elsewhere on the board
I2C_CTRL_SCL: Q901.4 (S2), U902.5 (SCL); also elsewhere on the board
I2C_CTRL_SDA: Q901.1 (S1), U902.4 (SDA); also elsewhere on the board
IO34: R908.2, U903.4 (EN); also elsewhere on the board
IO36: R906.2, U902.3 (Alert); also elsewhere on the board
unnamed: R907.1, U903.3 (ISET)
PORT_A0: RN901.8; also elsewhere on the board
PORT_A1: RN901.7; also elsewhere on the board
PORT_A2: RN901.6; also elsewhere on the board
PORT_A3: RN901.5; also elsewhere on the board
PORT_A4: RN902.8; also elsewhere on the board
PORT_A5: RN902.7; also elsewhere on the board
PORT_A6: RN902.6; also elsewhere on the board
PORT_A7: RN902.5; also elsewhere on the board
UP1: RN903.8; also elsewhere on the board
UP2: RN903.7; also elsewhere on the board
UP3: RN903.6; also elsewhere on the board
UP4: RN903.5; also elsewhere on the board
UP5: RN904.1; also elsewhere on the board
UP6: RN904.2; also elsewhere on the board
UP7: RN904.3; also elsewhere on the board
UP8: RN904.4; also elsewhere on the board
VCORE: C921.1, C923.1, D921.2 (K1), D921.5 (K2), D922.2 (K1), D922.5 (K2), D923.2 (K1), D923.5 (K2), D924.2 (K1), D924.5 (K2), D925.2 (K1), D925.5 (K2), D926.2 (K1), D926.5 (K2), D927.2 (K1), D927.5 (K2), D928.2 (K1), D928.5 (K2), Q901.2 (G1), Q901.5 (G2), R906.1, R908.1, U901.5 (MODE), U901.6 (VIN2), U902.6 (VS+); also elsewhere on the board
VPORT: C922.1, R905.2, U902.8 (VBUS), U902.9 (VIN-); also elsewhere on the board
VPORT_MUX: C924.1, U901.2 (VOUT), U901.7 (VOUT), U903.5 (IN)
VPORT_RAW: R905.1, U902.10 (VIN+), U903.1 (OUT)
VPORT_SEL: R904.1, U901.4 (PR1); also elsewhere on the board

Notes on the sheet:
Each package clamps two ESP GPIO lines to VCORE and GND.
U903 / U902 | VPORT LIMIT + MONITOR
VPORT = 3.3V (VIN2, default) or 5V (VIN1) selected by ESP32 IO40 (VPORT_SEL, high = 5V). VPORT feeds the AO6604 P-MOS of all 16 ports and their 100k gate pull-ups.
I2C level shifter: TCA9555 (U25, U73) now powered from 5V so they can switch the P-MOS gates with VPORT up to 5V.
Port protection (solution B): GPIO -> BAT54SDW clamp to VCORE/GND -> 330R -> PORT pin. Rule: no voltage above VPORT on any port pin. Firmware: set GPIO to hi-Z before turning a port to VCC/GND.
VPORT monitor: U902 INA226 @0x40 (A0=A1=GND) on I2C_CTRL. TPS2116 out = VPORT_MUX -> U903 SY6280 current limit ~1.9A (R907 3.6k, EN=IO34, R908 100k pull-up = on by default) -> VPORT_RAW -> shunt R905 50mR -> VPORT: 0.1V/0.2W @2A. VBUS reads VPORT (3.3V or 5V). ALERT (open drain) -> IO36 with R906 1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
RN901-RN904 | SERIES 330R (4x array)
GPIO -> 330R -> port pin. One symbol per physical array.
D921-D928 | GPIO CLAMP (BAT54SDW, SOT-363)
U901 | VPORT SELECT 3.3 V / 5 V
Q901 | I2C LEVEL SHIFTER
